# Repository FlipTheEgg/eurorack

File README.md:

# eurorack

A repository of eurorack hardware designed by me in KiCad.

## Overview:

### [HelloWorld](https://github.com/FlipTheEgg/eurorack/tree/master/HelloWorld)
My first module.

A three channel mixer with level control for in- and output.
Includes a detailed breakdown of the challenges and experiences of creating my first eurorack module. 

More to come!

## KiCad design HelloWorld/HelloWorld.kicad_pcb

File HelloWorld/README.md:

# HelloWorld

WIP

Hello World! This is a three-channel eurorack mixer based on the schematic of the [AI Synthesis AI002](http://aisynthesis.com/ai002-diy-eurorack-mixer-module-build/), but more importantly, as the name suggests, this is my first time doing several things. It's my first time...
 - Using KiCad
 - Making a eurorack module
 - Making something usable enough to give to someone (or maybe even sell)
 
I learned a lot in this process, and I wanted to document those experiences - for myself as well as others that could be interested in learning the same. 

If you're just here to make the module, go ahead and skip to [Can I make this?](https://github.com/FlipTheEgg/eurorack/tree/master/HelloWorld#can-i-make-this).
 
 ## How did I  do it?

I wanted to start out simple, so I chose a schematic i *completely* understood: a simple mixer with a volume control. AI Synthesis has a wonderful selection of well-documented DIY builds, including schematics and build guides, and I chose to copy the AI002 because the challenge with this project wasn't circuit design, but learning KiCad and designing to the specifications of Eurorack. My goal over time is to simultaneously design more sophisticated PCBs, and learn about more advanced circuits as I go.

With this specific project in mind I followed the guide [Getting Started in KiCad](https://docs.kicad-pcb.org/5.1/en/getting_started_in_kicad/getting_started_in_kicad.html), and substituted the example project with the AI002. I've previously experimented with [Fritzing](https://fritzing.org/), but I found it a little inaccurate and inflexible. Following the guide mostly went well and without issue. Not all the components I wanted to use had footprints in the standard Kicad library, but I managed to select some different components, or make my own footprints, which the guide also covers. I found KiCad to be slightly bulky to use at first, especially the disconnect between schematic symbol and footprint seemed cumbersome until I understood the flexibility this gives. I also had some confusion about how KiCad connects legs of the schematic components to the pins of the footprint (I can easily choose a 16-pin footprint to a 4-pin schematic component, for example), but  I realized that's where knowing how to edit footprints is really important and powerful. This also encouraged me to check the datasheets for my components whenever I was in doubt, which is good! The guide actually did answer almost all my questions, and upon revising my design, some of these quirks made more sense to me. For example, going back and choosing a different footprint or schematic symbol for a component, which I did a couple of times, was very quick and painless.

I also decided to design the panel as a PCB. I've seen this done on commercially available modules, and I think it looks good and seems both economical and practical. So I drew up a panel beside the main PCB (open the file HelloWorld.kicad_pcb to see how I did this), and followed the [Doepfer A100 Mechanical specification](http://www.doepfer.de/a100_man/a100m_e.htm) to see how to make the panel. I noticed that a lot of existing modules have oval mounting holes, which seemed smart. I also noticed that the Doepfer page said nothing about how tall my main PCB could be. Both of these problems were solved by measuring images of other modules on my screen, and calculating the length according to the known panel dimensions. This is not reccomended, *do* steal my findings from my schematics. I alsom made a custom footprint for the oval holes, as well as the holes for the potentiometers and the jacks. I might share these on GitHub at some point. Next time I think I'd like to make the PCB half a mm taller, so the offset, measured from the top and the bottom of the PCB, can be measured in whole mm's in relation to the panel. More on this measurement circus later. I later learned that having two boards in one file isn't as easy as I thought. KiCad handles it fine, but making it with a little breakoff part was incredibly difficult, and I couldn't figure it out. So I had to copy the main file, and make one file for the PCB and one for the panel. See (link...)

I realized that I needed a way to organize my Bill Of Materials (BOM) to keep track of what I needed to buy, so I made a spreadsheet where I listed and sourced my components, as well as held some other notes. This file is included in this repository, but it is a bit messy. I've deliberatly not cleaned it up, to give you an insight into how I worked. This process will likely be refined somehow. I chose to source my components at [Tayda](https://www.taydaelectronics.com/) and [Thonk](https://www.thonk.co.uk/) - more info in the BOM file.

Lastly I plotted the PCB to gerber files, ready to be manufactured, according to [the handy guide](https://support.jlcpcb.com/article/44-how-to-export-kicad-pcb-to-gerber-files) provided by my PCB manufacturer of choice, [JLCPCB](https://jlcpcb.com/). I reccommend following the guide for whereever you get them produced, it seems like they all have a lot of helpful information to help you to order correctly. I chose a black, Lead-free HASL board. Having the solder lead-free brought up the price a bit, but not by much. I made two seperate orders, one for the main board, and one for the panel, and ordered them together, choosing "europacket" as my shipping method. I'll report how it goes!

## What did I learn?
Here are some experiences I had, and some mistakes that I don't plan on repeating.
### Mils
While laying out the PCB, i quickly noticed that the standard grid wasn't in millimeters, but in [mils](https://en.wikipedia.org/wiki/Thousandth_of_an_inch). A mil is a thousandth of an inch, and 1 mil = 0.0254mm - making 10 mil just barely more than a quarter of a mm. This is apparently for historical reasons, but a lot of components are laid out with mil spacing between pins. I read somewhere that it has something to do with the tooling of PCB manufacturers, but I'm not really sure. What it meant for me, though, was that I had to change the grid to mm. The Doepfer eurorack standard is defined in millimeters, and some of the components are measured in mils, so that's a bit annoying. I prioritized  setting millimeter spacings between externals - jacks, pots - and place the rest in mils. If I place the other components in mm, I can't align my IC and my caps properly, which annoys me. So there was a bit of switching back and forth, but all in all it was OK.

### Footprints: decide what components to use *before* you layout.
This one I only thought about when shopping for components! I chose the footprints before I decided the exact components. This meant that when it came to decide what those were, I had accidentally limited my choice. In this case, it meant that I couldn't use box-type capacitors, because they have a much larger pin spaceing than I had selected. It also meant that I couldn't use a shrouded header for the power connector as originally planned, because I placed it too close to the edge without concern for its actual size. Speaking of the power header, I put it in the corner due to the Doepfer spec saying to place it there, but after looking at several popular modules I can conclude that the placement doesn't really matter. None of this was a problem, but I can easily imagine making an error like this resulting in having to redo the entire layout. Speaking of condensers, I just wanna plug [this great blogpost](http://tagboardeffects.blogspot.com/p/components.html) by Tagboardeffects about components. I've used it to understand especially what the differences are between condensers. Next time I'll try importing the [DigiKey Kicad Footprint Library](https://www.digikey.com/en/resources/design-tools/kicad), as I've read good things about it, and see if that helps.

### File structure and you: This repository is a mess...
...but it doesn't have to be this way! 
A lot of the confusion in the repository comes from how I exported the gerbers. I made seperate folders for the gerber files (smart), but put the zips outside of those folders (dumb). Next time I'll do it like this:

> **ProjectName**
>> other stuff
>>
>> **gerbers**
>>> FolderWithMainboard
>>>
>>> FolderWithPanel
>>>
>>> Mainboard.zip
>>>
>>> Panel.zip

I also have some redundancy on top of that, because I have a PCB file for the panel and the mainboard seperately, **AND** a file for both of them, du to how I split them originally. Next time I'll make a seperate PBC file for the panel from the get-go.

### Measure twice: Building the PCB before the panel is bad.
I accrued some technical debt by designing the PCB without having a plan for the placement of the components. When I was completely done with the main board, I had to measure where the jacks and pots went on the panel, correcting for the different sizes of the two. Luckily KiCad has a neat built-in ruler, but I had to make a lot of measurements. In the future, I'd vastly prefer placing the jacks and pots prior to designing the PCB.

### Panel design.
I really like the aesthetic of using a PCB as the panel, but there's room for improvement here. Using custom footprints, and clever design, you can do [some pretty incredible stuff](https://www.andrewsowa.com/sir-james-condi/). I'd like to start designing my panels using [Inkscape](https://inkscape.org/), and include custom graphics and logos and such, but I found it a bit difficult to also learn to use Inkscape i parallel. I did however find two promising tools for accomplishing this: [Svg2Shenzen](https://github.com/badgeek/svg2shenzhen) and [Synth Panels Designer](http://synthpanels.design/), both are plugins for Inkscape. Svg2Shenzen assists in managing the PCB layers and exporting to KiCad, and Synth Panels Designer helps make good looking scales for sliders and knobs, as well as having presets for panels in the correct sizes. I look forward to start designing better panels.

## Can I make this?
Yeah, go ahead! I wrote CC-BY-SA on the board, so I'm sticking with that. I don't know if this is the best license choice for this, if you know a bunch about it do reach out, I'd appreciate it. Send the gerber zip files to JLCPCB or someone else, and read the BOM to find out what parts you need, and order them somewhere. But **Don't** send them the zip with the panel *and* the main PCB, that'll go wrong. If you somehow do, please send me an image of the board you recieve.

## Resources: 
 - [KiCad](https://kicad-pcb.org/)
 - [Getting Started in KiCad](https://docs.kicad-pcb.org/5.1/en/getting_started_in_kicad/getting_started_in_kicad.html)
 - [AI Synthesis AI002 build guide](http://aisynthesis.com/ai002-diy-eurorack-mixer-module-build/) Schematic is under "resources".
 - [Befaco](https://www.befaco.org/) also has the schematics available for all their modules. They're all significantly more advanced than this build, but I'll definitely be looking at them in the future!
 - [Doepfer A100 electrical specification](http://www.doepfer.de/a100_man/a100t_e.htm)
 - [Doepfer A100 mechanical specification](http://www.doepfer.de/a100_man/a100m_e.htm)
 - [Tayda Electronics](https://www.taydaelectronics.com/) for parts
 - [Thonk](https://thonk.co.uk/) for more parts
 - [JLCPCB](https://jlcpcb.com/) for PCB manufacture
 - [How to export KiCad PCB to Gerber files](https://support.jlcpcb.com/article/44-how-to-export-kicad-pcb-to-gerber-files)
 - [Tagboardeffects - "Components"](http://tagboardeffects.blogspot.com/p/components.html)
 - [Inkscape](https://inkscape.org/)
 - [Svg2Shenzen](https://github.com/badgeek/svg2shenzhen)
 - [Synth Panels Designer](http://synthpanels.design/)
 - [DigiKey footprint library](https://www.digikey.com/en/resources/design-tools/kicad)

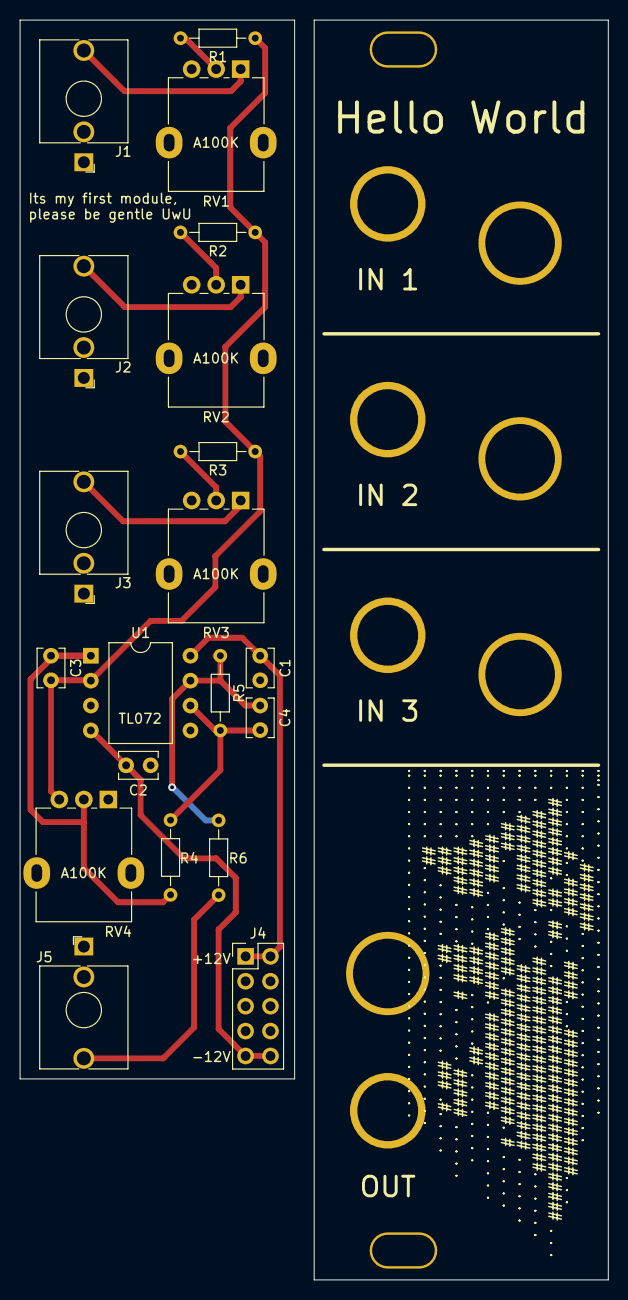
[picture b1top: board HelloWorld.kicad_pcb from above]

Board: 2 copper layers, 60.0 x 128.5 mm, 22 parts (0 on the bottom side), 14 nets.

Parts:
C1, C2: .1uF; C_Disc_D3.8mm_W2.6mm_P2.50mm
C3, C4: 47pF; C_Disc_D3.8mm_W2.6mm_P2.50mm
J1: IN1; Jack_3.5mm_QingPu_WQP-PJ398SM_Vertical_CircularHoles
J2: IN2; Jack_3.5mm_QingPu_WQP-PJ398SM_Vertical_CircularHoles
J3: IN3; Jack_3.5mm_QingPu_WQP-PJ398SM_Vertical_CircularHoles
J4: Conn_02x05_Odd_Even; PinHeader_2x05_P2.54mm_Vertical
J5: OUT; Jack_3.5mm_QingPu_WQP-PJ398SM_Vertical_CircularHoles
R1, R2, R3, R4, R5: 100K; R_Axial_DIN0204_L3.6mm_D1.6mm_P7.62mm_Horizontal
R6: 330R; R_Axial_DIN0204_L3.6mm_D1.6mm_P7.62mm_Horizontal
RV1, RV2, RV3, RV4: A100K; Potentiometer_Alpha_RD901F-40-00D_Single_Vertical
Ref**: 3.2mm-Mountinghole_Oval
Ref**#2: 3.2mm-Mountinghole_Oval
U1: TL072; DIP-8_W10.16mm

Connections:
+12V: C1.1, J4.1, J4.2, U1.8
-12V: C2.2, J4.9, J4.10, U1.4
GND: C1.2, C2.1, J1.S, J2.S, J3.S, J4.3, J4.4, J4.5, J4.6, J4.7, J4.8, J5.S, RV1.3, RV2.3, RV3.3, U1.3, U1.5
unnamed: C3.1, R4.2, RV4.2, U1.1
unnamed: C3.2, R1.1, R2.1, R3.1, RV4.3, U1.2
unnamed: C4.1, R5.1, R6.2, U1.7
unnamed: C4.2, R4.1, R5.2, U1.6
unnamed: J1.T, RV1.1
unnamed: J2.T, RV2.1
unnamed: J3.T, RV3.1
unnamed: J5.T, R6.1
unnamed: R1.2, RV1.2
unnamed: R2.2, RV2.2
unnamed: R3.2, RV3.2

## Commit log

2020-07-30 Update README.md
    Seeing if internal links work like I think they do
2020-07-30 added Doepfer links, text
2020-07-30 Update README.md
    Added link
2020-07-30 Update README.md
    formatting

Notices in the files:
HelloWorld/HelloWorld.kicad_pcb:
CC-BY-SA
HelloWorld/README.md:
Yeah, go ahead! I wrote CC-BY-SA on the board, so I'm sticking with that.
